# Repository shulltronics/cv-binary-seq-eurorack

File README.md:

## CV Binary Sequencer

This is a 1U Eurorack module that maps four trigger inputs to four CV outputs.
Inspired by the CV capabilities of Pamela's New Workout, _cv-binary-sequencer_ aims to produce customizable and intricate CV outputs for controlling other modules. There is a mapping of the 16 possible trigger inputs to a combination of CV outputs. On each trigger edge of an input CVs will change to the value specified by the mapping.

_cv-binary-seq_ can be used to multiplex 4 trigger inputs (e.g. 4 pads from a Beatstep Pro, or ) to create 16 different combinations of 4 CV outputs. This could be utilized to create 16 drum sounds from one module, or to create a 16 step melodic sequence that changes pitch, decay rate, and tone on each step.

### Goals
- [ ] - Configurable input trigger (rising, falling, etc). 
- [ ] - CV outputs similar to PNW (constant value, exponential rise/fall, period wave, etc).
- [ ] - Possibly add different input modes (binary mapping input to output, trigger input to cycle through mapping, etc).

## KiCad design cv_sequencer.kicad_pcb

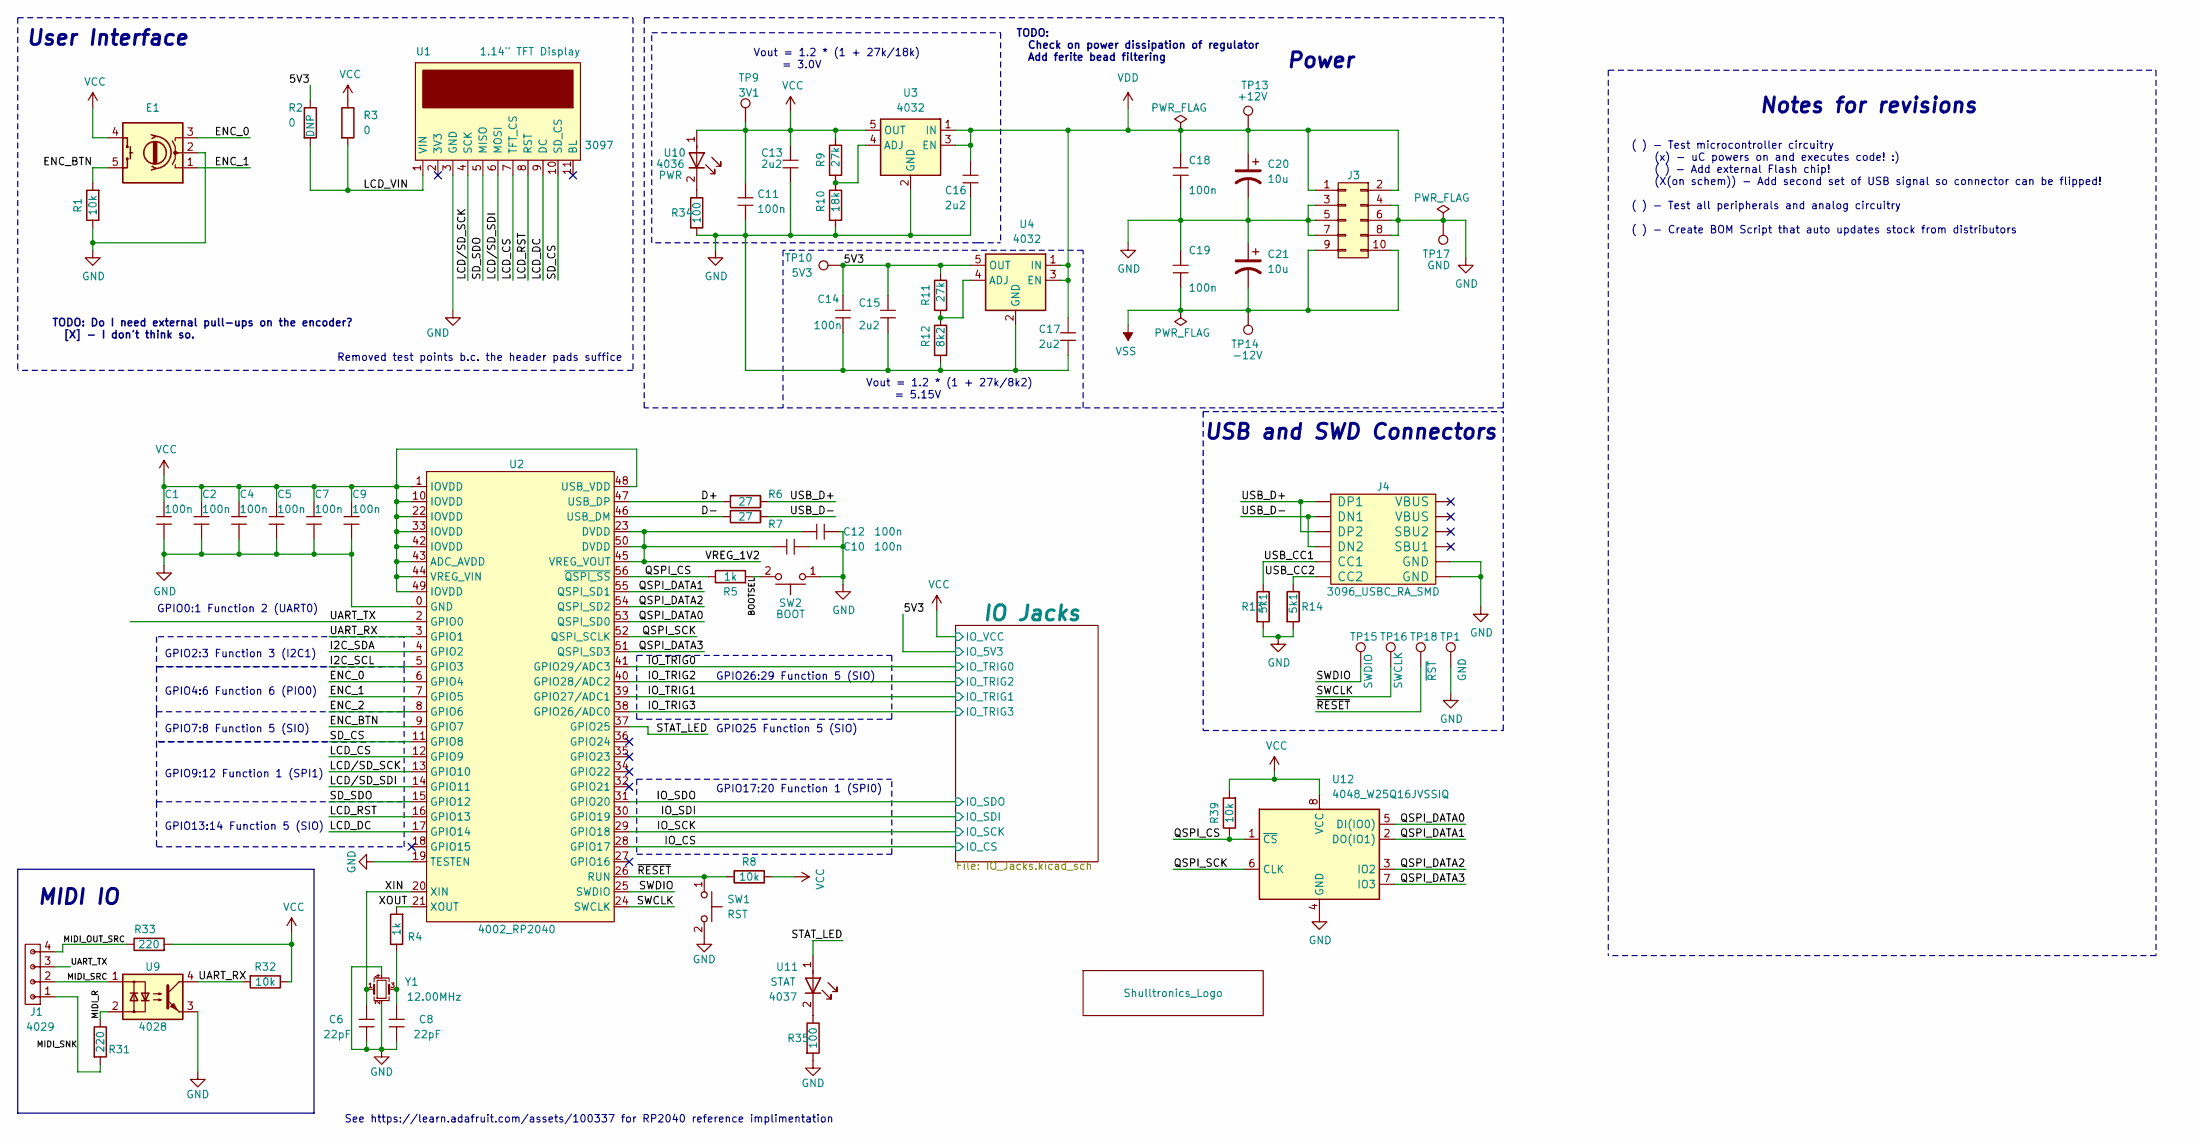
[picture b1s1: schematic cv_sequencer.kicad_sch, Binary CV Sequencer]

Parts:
C1, C2, C4, C5, C7, C9, C10, C11, C12, C14, C18, C19: 3089_Capacitor_100n_16V_0402; C_0402_HandSolder
C6, C8: 4003_Capacitor_22pF_50V_0402; C_0402_HandSolder
C13, C15, C16, C17: 4035_Capacitor_2u2_25V_0402; C_0402_HandSolder
C20, C21: 4031_Capacitor_10u_35V_SMD; 3088_Capacitor_10u_50V_SMD
E1: 4025_Encoder_Switch_SMD; 4025_Encoder_PEC11S
J1: :MIDI_IO; 4029_PicoBlade_4pos_Vert_THT
J3: 3086_Connector_Eurorack_Power; 3086_SMD_Eurorack_Power
J4: 3096_USBC_RA_SMD; 3096_USBC_RA
L1: Shulltronics_Logo
R1, R8, R32, R39: 4008_Resistor_SMD_10k_0.125W_1%; RES-0402
R2: DNP; RES-0402
R3: 4021_Resistor_SMD_Jumper; RES-0402
R4, R5: 4010_Resistor_SMD_1k_0.125W_1%; RES-0402
R6, R7: 4011_Resistor_SMD_27_0.125W_1%; RES-0402
R9, R11: 4016_Resistor_SMD_27k_0.125W_1%; RES-0402
R10: 4033_Resistor_SMD_18k_0.125W_1%; RES-0402
R12: 4034_Resistor_SMD_8k2_0.125W_1%; RES-0402
R13, R14: 4009_Resistor_SMD_5k1_0.10W_1%; RES-0402
R31, R33: 4030_Resistor_SMD_220_0.125W_1%; RES-0402
R34, R35: 4038_Resistor_SMD_100_0.125W_1%; RES-0402
SW1: RST; 4012_PushButton_NO_SMD
SW2: BOOT; 4012_PushButton_NO_SMD
TP1, TP17: GND; TestPoint_Pad_D2.0mm
TP9: 3V1; TestPoint_Pad_D2.0mm
TP10: 5V3; TestPoint_Pad_D2.0mm
TP13: +12V; TestPoint_Pad_D2.0mm
TP14: -12V; TestPoint_Pad_D2.0mm
TP15: SWDIO; TestPoint_Pad_D2.0mm
TP16: SWCLK; TestPoint_Pad_D2.0mm
TP18: ~{RST}; TestPoint_Pad_D2.0mm
U1: 3097_TFT_Display_SPI
U2: 4002_RP2040; 4002_RP2040_QFN-56-7x7mm_P0.4mm
U3, U4: 4032_Adjustable_Reg_200mA_SOT-23-5; SOT-23-5
U9: 4028_OptoIsolator_TLP290; 4028_OptoIsolator_TLP290_SOP-4
U10: PWR; LED_0402
U11: STAT; LED_0402
U12: 4048_W25Q16JVSSIQ; 4048_16Mb_Flash_SOIC8
Y1: 4004-Crystal-12MHz_GND24; 4004-Crystal-12MHz-4Pin_2.5x2.0mm

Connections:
/5V3: C14.2, C15.2, R2.1, R11.1, TP10.1, U4.5 (OUT); also elsewhere on the board
/BOOTSEL: R5.2, SW2.2
/D+: R6.2, U2.47 (USB_DP)
/D-: R7.2, U2.46 (USB_DM)
/ENC_0: E1.3, U2.6 (GPIO4)
/ENC_1: E1.1, U2.7 (GPIO5)
/ENC_2: U2.8 (GPIO6)
/ENC_BTN: E1.5, R1.2, U2.9 (GPIO7)
/I2C_SCL: U2.5 (GPIO3)
/I2C_SDA: U2.4 (GPIO2)
/IO_CS: U2.28 (GPIO17); also elsewhere on the board
/IO_SCK: U2.29 (GPIO18); also elsewhere on the board
/IO_SDI: U2.30 (GPIO19); also elsewhere on the board
/IO_SDO: U2.31 (GPIO20); also elsewhere on the board
/IO_TRIG0: U2.41 (GPIO29/ADC3); also elsewhere on the board
/IO_TRIG1: U2.39 (GPIO27/ADC1); also elsewhere on the board
/IO_TRIG2: U2.40 (GPIO28/ADC2); also elsewhere on the board
/IO_TRIG3: U2.38 (GPIO26/ADC0); also elsewhere on the board
/LCD_CS: U1.7 (TFT_CS), U2.12 (GPIO9)
/LCD_DC: U1.9 (DC), U2.17 (GPIO14)
/LCD_RST: U1.8 (RST), U2.16 (GPIO13)
/LCD_VIN: R2.2, R3.2, U1.1 (VIN)
/LCD/SD_SCK: U1.4 (SCK), U2.13 (GPIO10)
/LCD/SD_SDI: U1.6 (MOSI), U2.14 (GPIO11)
/MIDI_OUT_SRC: J1.4, R33.1
/MIDI_R: R31.1, U9.2
/MIDI_SNK: J1.1, R31.2
/MIDI_SRC: J1.2, U9.1
/QSPI_CS: R5.1, R39.1, U2.56 (~QSPI_SS), U12.1 (~CS)
/QSPI_DATA0: U2.53 (QSPI_SD0), U12.5 (DI(IO0))
/QSPI_DATA1: U2.55 (QSPI_SD1), U12.2 (DO(IO1))
/QSPI_DATA2: U2.54 (QSPI_SD2), U12.3 (IO2)
/QSPI_DATA3: U2.51 (QSPI_SD3), U12.7 (IO3)
/QSPI_SCK: U2.52 (QSPI_SCLK), U12.6 (CLK)
/SD_CS: U1.10 (SD_CS), U2.11 (GPIO8)
/SD_SDO: U1.5 (MISO), U2.15 (GPIO12)
/STAT_LED: U2.37 (GPIO25), U11.1 (A)
/SWCLK: TP16.1, U2.24 (SWCLK)
/SWDIO: TP15.1, U2.25 (SWDIO)
/UART_RX: R32.2, U2.3 (GPIO1), U9.4
/UART_TX: J1.3, U2.2 (GPIO0)
/USB_CC1: J4.A5 (CC1), R13.1
/USB_CC2: J4.B5 (CC2), R14.1
/USB_D+: J4.A6 (DP1), J4.B6 (DP2), R6.1
/USB_D-: J4.A7 (DN1), J4.B7 (DN2), R7.1
/VREG_1V2: C10.1, C12.1, U2.23 (DVDD), U2.45 (VREG_VOUT), U2.50 (DVDD)
/XIN: C6.2, U2.20 (XIN), Y1.1
/XOUT: R4.2, U2.21 (XOUT)
/~RESET: R8.1, SW1.1, TP18.1, U2.26 (RUN)
GND: C1.1, C2.1, C4.1, C5.1, C6.1, C7.1, C8.1, C9.1, C10.2, C11.1, C12.2, C13.1, C14.1, C15.1, C16.1, C17.1, C18.1, C19.2, C20.2, C21.1, E1.2, J3.3, J3.4, J3.5, J3.6, J3.7, J3.8, J4.A1/B12 (GND), J4.B1/A12 (GND), R1.1, R10.2, R12.2, R13.2, R14.2, R34.2, R35.2, SW1.2, SW2.1, TP1.1, TP17.1, U1.3 (GND), U2.0 (GND), U2.19 (TESTEN), U3.2 (GND), U4.2 (GND), U9.3, U12.4 (GND), Y1.2, Y1.4; also elsewhere on the board
unnamed: C8.2, R4.1, Y1.3
unnamed: R9.2, R10.1, U3.4 (ADJ)
unnamed: R11.2, R12.1, U4.4 (ADJ)
unnamed: R34.1, U10.2 (K)
unnamed: R35.1, U11.2 (K)
VCC: C1.2, C2.2, C4.2, C5.2, C7.2, C9.2, C11.2, C13.2, E1.4, R3.1, R8.2, R9.1, R32.1, R33.2, R39.2, TP9.1, U2.1 (IOVDD), U2.10 (IOVDD), U2.22 (IOVDD), U2.33 (IOVDD), U2.42 (IOVDD), U2.43 (ADC_AVDD), U2.44 (VREG_VIN), U2.48 (USB_VDD), U2.49 (IOVDD), U3.5 (OUT), U10.1 (A), U12.8 (VCC); also elsewhere on the board
VDD: C16.2, C17.2, C18.2, C20.1, J3.1, J3.2, TP13.1, U3.1 (IN), U3.3 (EN), U4.1 (IN), U4.3 (EN); also elsewhere on the board
VSS: C19.1, C21.2, J3.9, J3.10, TP14.1; also elsewhere on the board

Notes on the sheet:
GPIO25 Function 5 (SIO)
Vout = 1.2 * (1 + 27k/8k2) = 5.15V
GPIO2:3 Function 3 (I2C1)
GPIO17:20 Function 1 (SPI0)
Removed test points b.c. the header pads suffice
See https://learn.adafruit.com/assets/100337 for RP2040 reference implimentation
Vout = 1.2 * (1 + 27k/18k) = 3.0V
GPIO7:8 Function 5 (SIO)
USB and SWD Connectors
( ) - Test microcontroller circuitry (x) - uC powers on and executes code! :) ( ) - Add external Flash chip! (X(on schem)) - Add second set of USB signal so connector can be flipped! ( ) - Test all peripherals and analog circuitry ( ) - Create BOM Script that auto updates stock from distributors
GPIO9:12 Function 1 (SPI1)
TODO: Do I need external pull-ups on the encoder? [X] - I don't think so.
Notes for revisions
MIDI IO
GPIO0:1 Function 2 (UART0)
GPIO26:29 Function 5 (SIO)
Power
TODO: Check on power dissipation of regulator Add ferite bead filtering
GPIO13:14 Function 5 (SIO)
GPIO4:6 Function 6 (PIO0)
User Interface

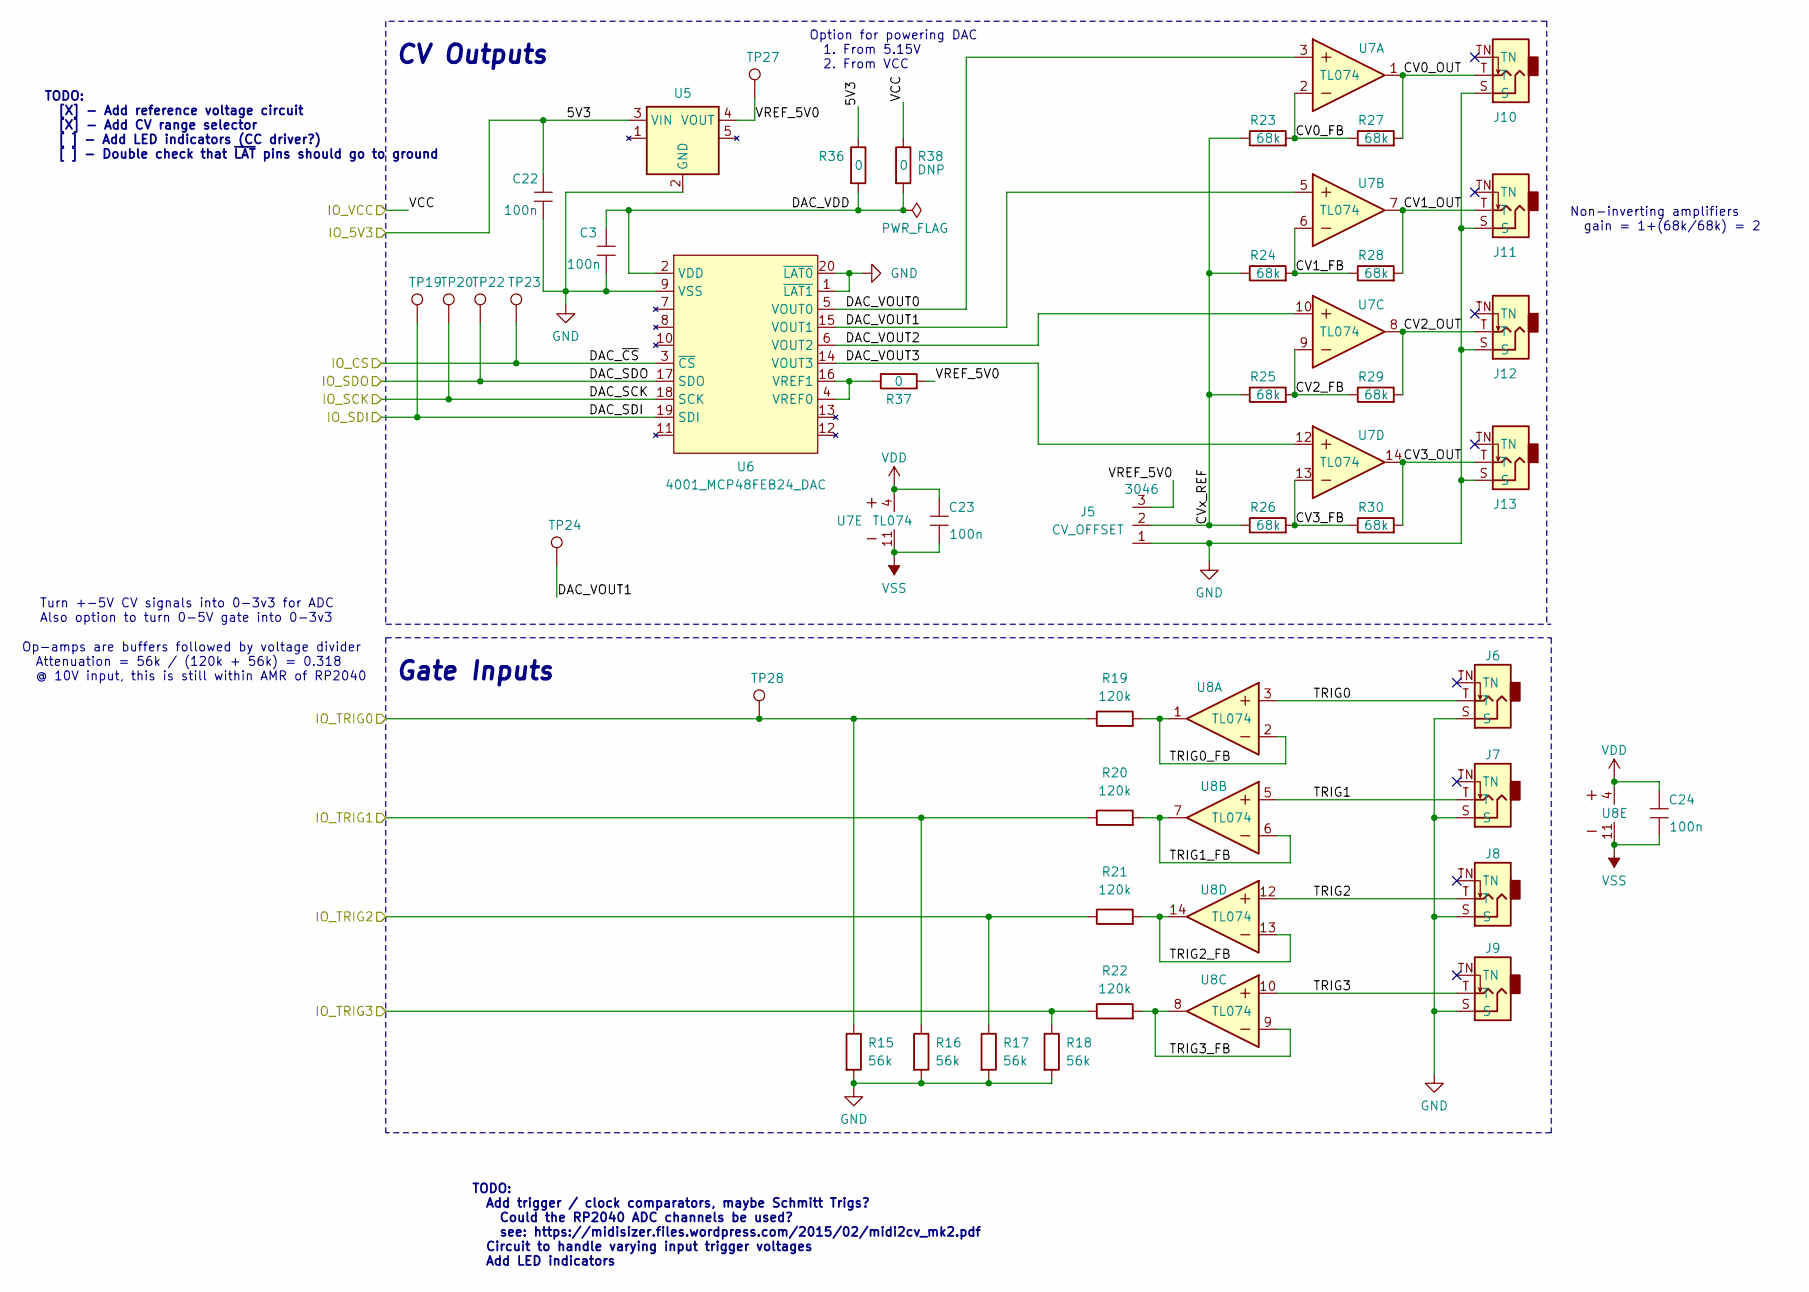
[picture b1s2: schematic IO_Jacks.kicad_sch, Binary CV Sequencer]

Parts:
C3, C22, C23, C24: 3089_Capacitor_100n_16V_SMD; C_0402_HandSolder
J5: CV_OFFSET; SMD_SolderJumper-3
J6, J7, J8, J9, J10, J11, J12, J13: 3085_MiniJack_Thonk_Vert
R15, R16, R17, R18: 4023_Resistor_SMD_56k_0.125W_1%; RES-0402
R19, R20, R21, R22: 4022_Resistor_SMD_120k_0.125W_1%; RES-0402
R23, R24, R25, R26, R27, R28, R29, R30: 4006_Resistor_SMD_68k_0.125W_1%; RES-0402
R36: 4021_Resistor_SMD_Jumper; RES-0402
R37: JMP; RES-0402
R38: DNP; RES-0402
TP19: SDI; TestPoint_Pad_D2.0mm
TP20: SCK; TestPoint_Pad_D2.0mm
TP22: SDO; TestPoint_Pad_D2.0mm
TP23: ~{CS}; TestPoint_Pad_D2.0mm
TP24: DAC1; TestPoint_Pad_D2.0mm
TP27: 5V0; TestPoint_Pad_D2.0mm
TP28: TRIG0; TestPoint_Pad_D2.0mm
U5: 4014_Voltage_Reference_5V_SOT23-6; SOT-23-5
U6: 4001_MCP48FEB24_DAC; TSSOP-20_4.4x6.5mm_P0.65mm
U7, U8: 3099_TL074CPW_SMD; 3099_TL074CPW_TSSOP14

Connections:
/5V3: C22.2, R36.1, U5.3 (VIN); also elsewhere on the board
/IO Jacks/CV0_FB: R23.2, R27.1, U7.2 (1IN-)
/IO Jacks/CV0_OUT: J10.T, R27.2, U7.1 (1OUT)
/IO Jacks/CV1_FB: R24.2, R28.1, U7.6 (2IN-)
/IO Jacks/CV1_OUT: J11.T, R28.2, U7.7 (2OUT)
/IO Jacks/CV2_FB: R25.2, R29.1, U7.9 (3IN-)
/IO Jacks/CV2_OUT: J12.T, R29.2, U7.8 (3OUT)
/IO Jacks/CV3_FB: R26.2, R30.1, U7.13 (4IN-)
/IO Jacks/CV3_OUT: J13.T, R30.2, U7.14 (4OUT)
/IO Jacks/CVx_REF: J5.2, R23.1, R24.1, R25.1, R26.1
/IO Jacks/DAC_VDD: C3.2, R36.2, R38.2, U6.2 (VDD)
/IO Jacks/DAC_VOUT0: U6.5 (VOUT0), U7.3 (1IN+)
/IO Jacks/DAC_VOUT1: TP24.1, U6.15 (VOUT1), U7.5 (2IN+)
/IO Jacks/DAC_VOUT2: U6.6 (VOUT2), U7.10 (3IN+)
/IO Jacks/DAC_VOUT3: U6.14 (VOUT3), U7.12 (4IN+)
/IO Jacks/TRIG0: J6.T, U8.3 (1IN+)
/IO Jacks/TRIG0_FB: R19.2, U8.1 (1OUT), U8.2 (1IN-)
/IO Jacks/TRIG1: J7.T, U8.5 (2IN+)
/IO Jacks/TRIG1_FB: R20.2, U8.6 (2IN-), U8.7 (2OUT)
/IO Jacks/TRIG2: J8.T, U8.12 (4IN+)
/IO Jacks/TRIG2_FB: R21.2, U8.13 (4IN-), U8.14 (4OUT)
/IO Jacks/TRIG3: J9.T, U8.10 (3IN+)
/IO Jacks/TRIG3_FB: R22.2, U8.8 (3OUT), U8.9 (3IN-)
/IO Jacks/VREF_5V0: J5.3, R37.1, TP27.1, U5.4 (VOUT)
/IO_CS: TP23.1, U6.3 (~CS); also elsewhere on the board
/IO_SCK: TP20.1, U6.18 (SCK); also elsewhere on the board
/IO_SDI: TP19.1, U6.19 (SDI); also elsewhere on the board
/IO_SDO: TP22.1, U6.17 (SDO); also elsewhere on the board
/IO_TRIG0: R15.1, R19.1, TP28.1; also elsewhere on the board
/IO_TRIG1: R16.1, R20.1; also elsewhere on the board
/IO_TRIG2: R17.1, R21.1; also elsewhere on the board
/IO_TRIG3: R18.1, R22.1; also elsewhere on the board
GND: C3.1, C22.1, J5.1, J6.S, J7.S, J8.S, J9.S, J10.S, J11.S, J12.S, J13.S, R15.2, R16.2, R17.2, R18.2, U5.2 (GND), U6.1 (~LAT1), U6.9 (VSS), U6.20 (~LAT0); also elsewhere on the board
unnamed: R37.2, U6.4 (VREF0), U6.16 (VREF1)
VCC: R38.1; also elsewhere on the board
VDD: C23.2, C24.2, U7.4 (VCC), U8.4 (VCC); also elsewhere on the board
VSS: C23.1, C24.1, U7.11 (VEE), U8.11 (VEE); also elsewhere on the board

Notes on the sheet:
TODO: [X] - Add reference voltage circuit [X] - Add CV range selector [ ] - Add LED indicators (CC driver?) [ ] - Double check that ~{LAT} pins should go to ground
Gate Inputs
Turn +-5V CV signals into 0-3v3 for ADC Also option to turn 0-5V gate into 0-3v3
CV Outputs
Op-amps are buffers followed by voltage divider Attenuation = 56k / (120k + 56k) = 0.318 @ 10V input, this is still within AMR of RP2040
Option for powering DAC 1. From 5.15V 2. From VCC
TODO: Add trigger / clock comparators, maybe Schmitt Trigs? Could the RP2040 ADC channels be used? see: https://midisizer.files.wordpress.com/2015/02/midi2cv_mk2.pdf Circuit to handle varying input trigger voltages Add LED indicators
Non-inverting amplifiers gain = 1+(68k/68k) = 2

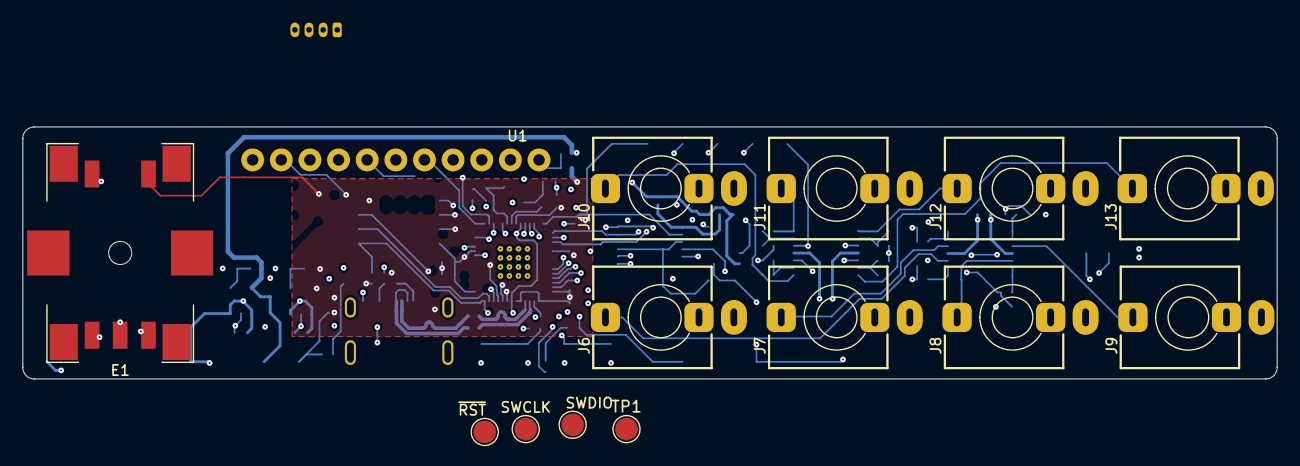
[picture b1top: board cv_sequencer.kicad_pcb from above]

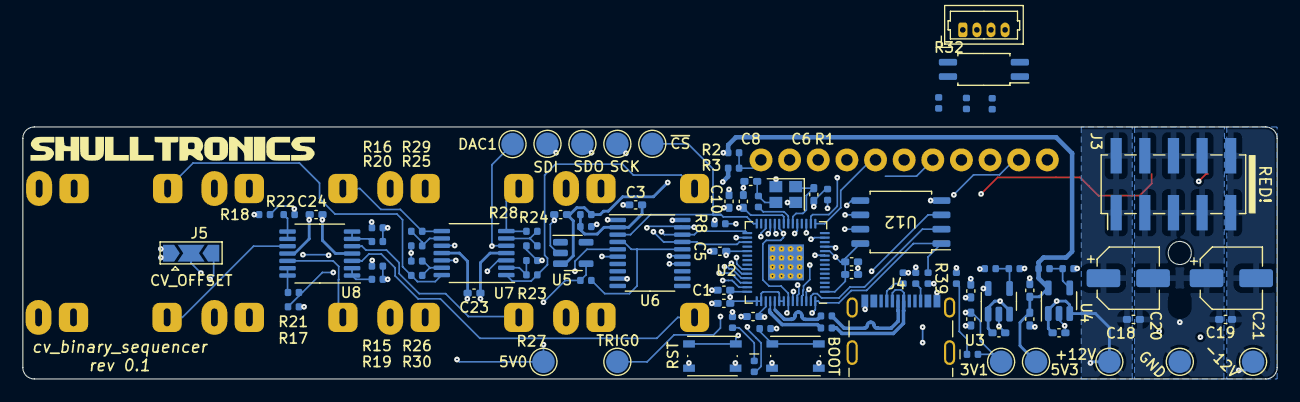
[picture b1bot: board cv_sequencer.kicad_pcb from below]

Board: 4 copper layers, 111.3 x 22.4 mm, 108 parts (94 on the bottom side), 79 nets.

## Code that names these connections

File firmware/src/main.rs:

#![no_std]
#![no_main]

use panic_halt as _;
use cortex_m::prelude::*;
use cortex_m_rt::entry;
use embedded_hal::{
    digital::v2::{OutputPin, InputPin}
};
// use embedded_time::rate::*;
use fugit::RateExtU32;  // allows the .to_Hz() method
use rp2040_hal as hal;
use hal::{
    clocks::{init_clocks_and_plls, Clock},
    pac,
    pac::interrupt,
    watchdog::Watchdog,
    Sio,
    gpio::Pins,
};

use display_interface_spi::SPIInterface;
use st7789::{Orientation, ST7789};
use embedded_graphics::{
    prelude::*,
    primitives::*,
    pixelcolor::Rgb565,
    mono_font::{ascii::FONT_6X9, MonoTextStyle},
    text::Text,
};

mod mcp48fxbxx;
use mcp48fxbxx::MCP48FXBxx;

/// The linker will place this boot block at the start of our program image. We
/// need this to help the ROM bootloader get our code up and running.
#[link_section = ".boot2"]
#[used]
pub static BOOT2: [u8; 256] = rp2040_boot2::BOOT_LOADER_RAM_MEMCPY;
const XTAL_OSC_FREQ: u32 = 12_000_000;

// USB Device support
// use usb_device::class_prelude::*;
// // USB Communications Class Device support
// mod usb_manager;
// use usb_manager::UsbManager;
// /******************************************************************************
//      Global USB objects & interrupt
// ******************************************************************************/
// static mut USB_BUS: Option<UsbBusAllocator<hal::usb::UsbBus>> = None;
// static mut USB_MANAGER: Option<UsbManager> = None;
// #[allow(non_snake_case)]
// #[interrupt]
// unsafe fn USBCTRL_IRQ() {
//     match USB_MANAGER.as_mut() {
//         Some(manager) => manager.interrupt(),
//         None => (),
//     };
// }

#[entry]
fn main() -> ! {
    // initialization code here
    let mut pac = pac::Peripherals::take().unwrap();
    let core = pac::CorePeripherals::take().unwrap();
    let mut watchdog = Watchdog::new(pac.WATCHDOG);

    let clocks = init_clocks_and_plls(
        XTAL_OSC_FREQ,
        pac.XOSC,
        pac.CLOCKS,
        pac.PLL_SYS,
        pac.PLL_USB,
        &mut pac.RESETS,
        &mut watchdog,
    ).ok().unwrap();

    let sio = Sio::new(pac.SIO);
    let pins = Pins::new(
        pac.IO_BANK0,
        pac.PADS_BANK0,
        sio.gpio_bank0,
        &mut pac.RESETS,
    );

    // Setup USB
    // let usb = unsafe {
    //     USB_BUS = Some(UsbBusAllocator::new(hal::usb::UsbBus::new(
    //         pac.USBCTRL_REGS,
    //         pac.USBCTRL_DPRAM,
    //         clocks.usb_clock,
    //         true,
    //         &mut pac.RESETS,
    //     )));
    //     USB_MANAGER = Some(UsbManager::new(USB_BUS.as_ref().unwrap()));
    //     // Enable the USB interrupt
    //     pac::NVIC::unmask(hal::pac::Interrupt::USBCTRL_IRQ);
    //     USB_MANAGER.as_mut().unwrap()
    // };


    let mut timer = cortex_m::delay::Delay::new(core.SYST, clocks.system_clock.freq().to_Hz());
    
    // general purpose testing pin (goes to unpopulated LED for now)
    let mut status_pin = pins.gpio25.into_push_pull_output();
    status_pin.set_high().unwrap();
    let encoder_button = pins.gpio7.into_pull_down_input();

    // pins for use with ST7789 LCD
    let _lcd_cs  = pins.gpio9.into_push_pull_output();
    let _lcd_sclk = pins.gpio10.into_mode::<hal::gpio::FunctionSpi>();
    let _lcd_mosi = pins.gpio11.into_mode::<hal::gpio::FunctionSpi>();
    let _lcd_miso = pins.gpio12.into_mode::<hal::gpio::FunctionSpi>();
    let _lcd_rst = pins.gpio13.into_push_pull_output();
    let _lcd_dc  = pins.gpio14.into_push_pull_output();
    // // initialize the SPI module
    let spi = hal::Spi::<_, _, 8>::new(pac.SPI1);
    let mut spi = spi.init(
        &mut pac.RESETS,
        clocks.peripheral_clock.freq(),
        10_000_000u32.Hz(),
        &embedded_hal::spi::MODE_3,
    );
    // create the SPI "display interface"
    let di = SPIInterface::new(spi, _lcd_dc, _lcd_cs);
    let mut lcd = ST7789::new(di, _lcd_rst, 240, 135);
    // // initialize the display and set its orientation
    lcd.init(&mut timer).unwrap();
    lcd.set_orientation(Orientation::Landscape).unwrap();

    // let line = Line::new(Point::new(0, 0), Point::new(100, 100))
    //     .into_styled(PrimitiveStyle::with_stroke(Rgb565::WHITE, 1));
    lcd.clear(Rgb565::WHITE).unwrap();
    // line.draw(&mut lcd).unwrap();

    let style = MonoTextStyle::new(&FONT_6X9, Rgb565::RED);
    let mut text = Text::new("hello, rust!", Point::new(100, 100), style);
    
    /**************************************************************************
    MCP DAC Setup and Testing
    **************************************************************************/
    let _dac_cs   = pins.gpio17.into_push_pull_output();
    let _dac_sclk = pins.gpio18.into_mode::<hal::gpio::FunctionSpi>();
    let _dac_mosi = pins.gpio19.into_mode::<hal::gpio::FunctionSpi>();
    let _dac_miso = pins.gpio20.into_mode::<hal::gpio::FunctionSpi>();
    // // initialize the SPI module
    let spi0 = hal::Spi::<_, _, 8>::new(pac.SPI0);
    let mut spi0 = spi0.init(
        &mut pac.RESETS,
        clocks.peripheral_clock.freq(),
        10_000_000u32.Hz(),
        &embedded_hal::spi::MODE_3,
    );
    // Create the driver object
    let mut dac = MCP48FXBxx::new(spi0, _dac_cs);
    dac.init();
    // try reading from a register
    let res = dac.read();
    // dac.write(0xAA);
    dac.setup();

    // loop code here
    let mut old_button_state: bool = false;
    loop {
        let current_button_state: bool = encoder_button.is_high().unwrap();
        let button_changed: bool = (old_button_state != current_button_state);
        if button_changed {
            old_button_state = current_button_state;
            if current_button_state == true {
                text.draw(&mut lcd).unwrap();
            } else {
                lcd.clear(Rgb565::BLACK).unwrap();
            }
        }
    }
}

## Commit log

2022-03-09 Start tracking work on this project
2022-03-10 added gitignore to not track backups
2022-03-10 fleshed out a lot of the MCU circuitry
2022-03-10 worked on gate input circuitry
2022-03-11 finished schematic (still needs double checking)
2022-03-11 ran ERC, minimal errors. Imported footprints and started grouping them
2022-03-14 more work on pcb, added some TODO notes to schematic
2022-03-14 Changed encoder to SMD version
2022-03-15 gots most components placed nicely, added 4027 for MIDI, still to finish
2022-03-15 Made minor tweaks, started routing of board
2022-03-16 some more routing
2022-03-16 Added a few 0 ohm options, finished routing, ordered board!
2022-03-28 updated jack and encoder footprints with user drawing layer
2022-04-07 Started firmware. Didn't realize RP2040 needed external flash. But luckily found linker script that can load and execute code straight from RAM
2022-04-07 minimal example with LCD and button working. Stop tracking build artifacts
2022-06-23 Added README and PCB rev1 photos
2022-06-23 Tweak to README
2023-01-17 Updated library versions, migrated to fugit
2023-01-17 stop tracking lock file
2023-01-17 Started work on DAC module
2023-01-18 Verified SPI0 signals with scope, next it try to talk with DAC
2023-01-18 Verified that DAC is recieving SPI transactions and outputing correctly!
2023-01-22 Changes from a while ago
2023-01-22 Added USB other-side connections to schematic
2023-01-24 Added QSPI Flash to Schematic
2023-01-24 Started re-route of PCB
2023-01-24 Routed Flash chip.. need to figure out second set of USB lines
2023-01-30 Updated a few things from testing voltage regulators
2023-01-31 Added components and routed for 5v0 reference
2024-09-10 updated to KiCad v8
